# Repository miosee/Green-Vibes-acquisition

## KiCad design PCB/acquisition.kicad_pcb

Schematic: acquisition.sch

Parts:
C1: 220u; CP_Radial_D10.0mm_P5.00mm
J1: Coil; PinHeader_1x02_P2.54mm_Vertical
J2: potentiometer; PinHeader_1x02_P2.54mm_Vertical
J3: Accelerometer; PinSocket_1x05_P2.54mm_Vertical
J4: LCD; PinHeader_1x10_P2.54mm_Vertical
R1, R4: 15k; R_Axial_DIN0207_L6.3mm_D2.5mm_P10.16mm_Horizontal
R2, R3: 7.5k; R_Axial_DIN0207_L6.3mm_D2.5mm_P10.16mm_Horizontal
R5, R8: 51k; R_Axial_DIN0207_L6.3mm_D2.5mm_P10.16mm_Horizontal
R6: 1k; R_Axial_DIN0207_L6.3mm_D2.5mm_P10.16mm_Horizontal
R7: 1; R_Axial_DIN0207_L6.3mm_D2.5mm_P10.16mm_Horizontal
R9: 2k; R_Axial_DIN0207_L6.3mm_D2.5mm_P10.16mm_Horizontal
RV1: 10k; Potentiometer_Bourns_3296W_Vertical
U1, U2: MCP6271; DIP-8_W7.62mm
U3: Arduino_Nano_v3.x; Arduino_Nano

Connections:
+5V: C1.1, J3.1, J4.1, R1.1, R5.1, RV1.3, U1.7 (V+), U2.7 (V+), U3.27 (+5V)
/DB4: J4.7, U3.9 (D6)
/DB5: J4.8, U3.10 (D7)
/DB6: J4.9, U3.11 (D8)
/DB7: J4.10, U3.12 (D9)
/E: J1.1, J2.1, R2.2
/Enable: J4.6, U3.8 (D5)
/I: J2.2, R6.2, R7.1
/INT: J3.5, U3.5 (D2)
/RS: J4.5, U3.7 (D4)
/SCL: J3.4, U3.24 (A5)
/SDA: J3.3, U3.23 (A4)
/VO: J4.2, RV1.2
/Ve: R3.1, U1.6, U3.19 (A0)
/Vi: R8.1, U2.6, U3.20 (A1)
GND: C1.2, J1.2, J3.2, J4.3, J4.4, R4.2, R7.2, R9.2, RV1.1, U1.4 (V-), U2.4 (V-), U3.4 (GND), U3.29 (GND)
unnamed: R1.2, R2.1, U1.3 (+)
unnamed: R3.2, R4.1, U1.2 (-)
unnamed: R5.2, R6.1, U2.3 (+)
unnamed: R8.2, R9.1, U2.2 (-)

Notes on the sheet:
Ve = E + 2.5V
Vi = 26*I(A) + 2.55V

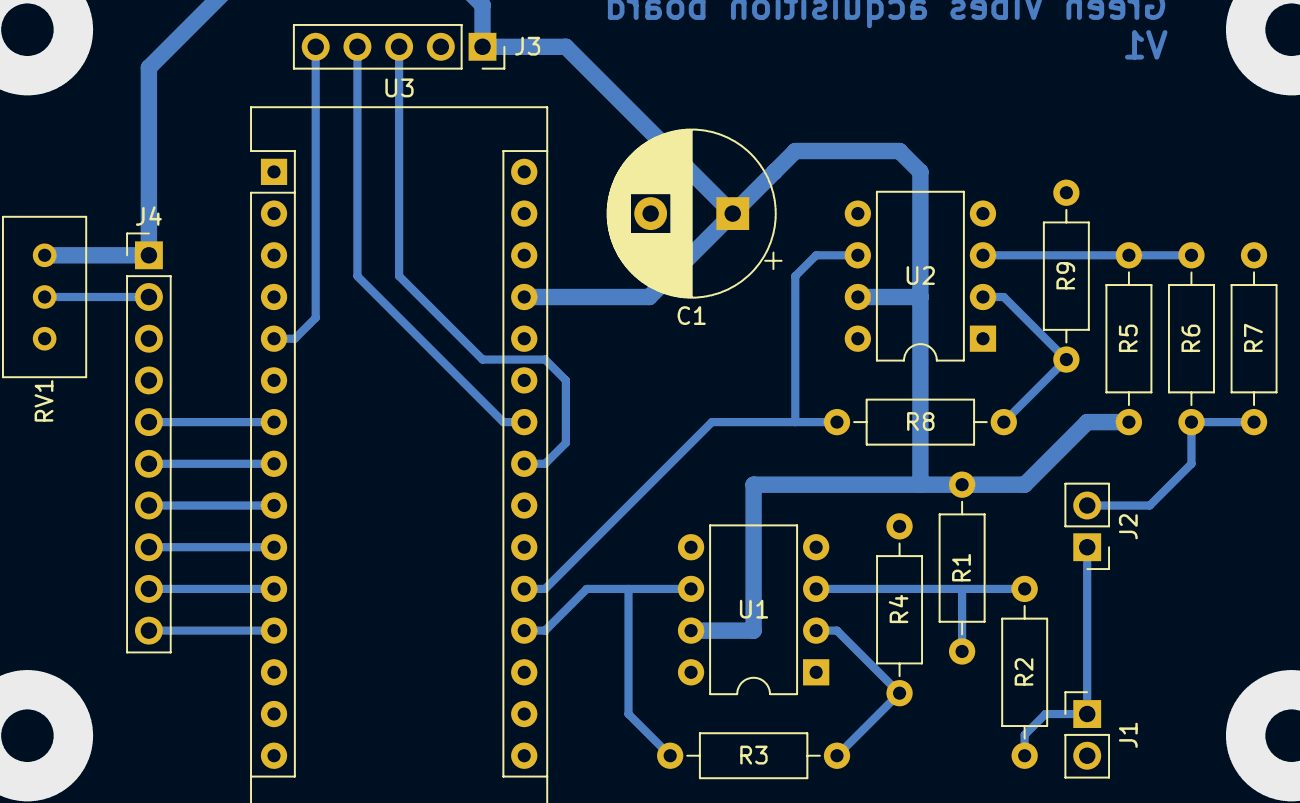
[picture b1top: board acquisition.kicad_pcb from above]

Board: 2 copper layers, 18 parts (0 on the bottom side), 20 nets.

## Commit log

2021-07-13 First version
    Electronics schematics
    Arduino firmware
    Python interface
2021-07-13 good first version
2021-10-04 Ajout du PCB Mise à jour du code arduino et du code python
2021-10-19 version du WE
